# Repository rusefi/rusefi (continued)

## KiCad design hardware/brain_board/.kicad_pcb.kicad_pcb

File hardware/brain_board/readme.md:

Brain board stm 100 pin

[Forum post](https://rusefi.com/forum/viewtopic.php?f=4&t=381)

[Known issues](known_issues.txt)

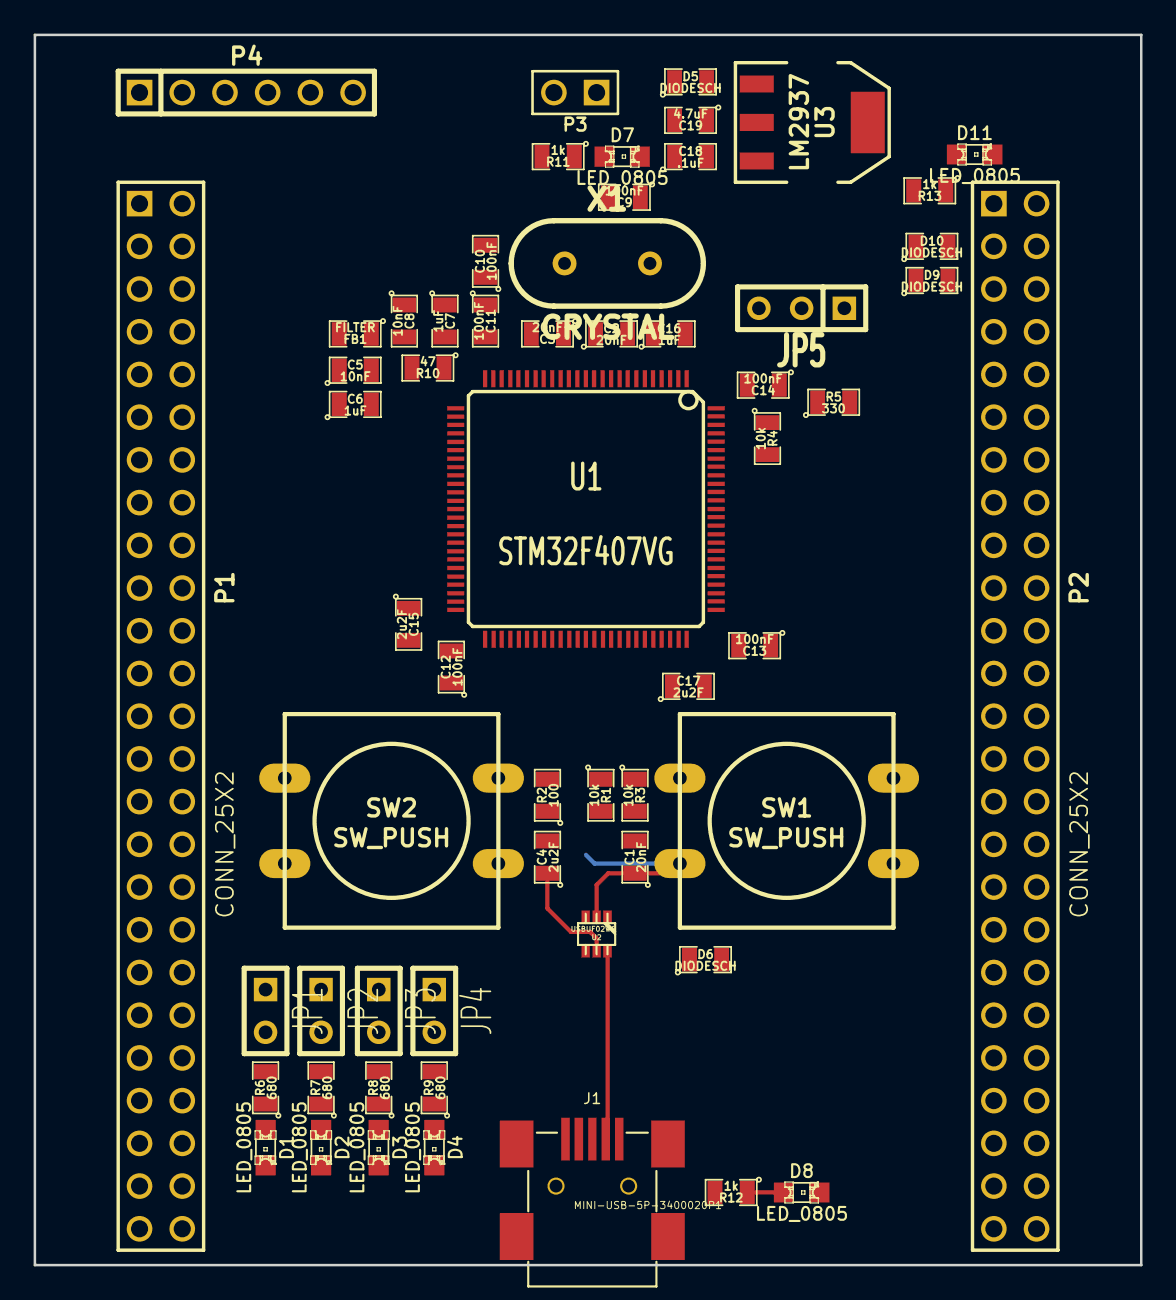
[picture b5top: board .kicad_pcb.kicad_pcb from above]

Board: 2 copper layers, 65.8 x 73.2 mm, 61 parts (1 on the bottom side), 112 nets.

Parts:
BT1: BATTERY_CR2032; BATT_CR2032_MPD
C1, C2, C3: 20nF; SM0805
C4, C15, C17: 2u2F; SM0805
C5, C8: 10nF; SM0805
C6, C7, C16: 1uF; SM0805
C9, C10, C11, C12, C13, C14: 100nF; SM0805
C18: .1uF; SM0805
C19: 4.7uF; SM0805
D1, D2, D3, D4, D7, D8, D11: LED_0805; LED-0805_A
D5, D6, D9, D10: DIODESCH; SM0805
FB1: FILTER; SM0805
J1: MINI-USB-5P-3400020P1
JP1, JP2, JP3, JP4: JUMPER; JUMPER-2
JP5: JUMPER3; SIL-3
P1, P2: CONN_25X2; PIN_ARRAY_25x2_A
P3: CONN_2; PIN_ARRAY_2_A
P4: CONN_6; PIN_ARRAY-6X1
R1, R3, R4: 10k; SM0805
R2: 100; SM0805
R5: 330; SM0805
R6, R7, R8, R9: 680; SM0805
R10: 47; SM0805
R11, R12, R13: 1k; SM0805
SW1, SW2: SW_PUSH; SW_PUSH-12mm
U1: STM32F407VG; TQFP_100
U2: USBUF02W6; sot323-6
U3: LM2937; SOT223
X1: CRYSTAL; HC-49V

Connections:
/3V: D9.2, P2.5, P2.6
/5V: D10.2, P2.3, P2.4
/5Vi: C18.2, C19.1, D5.2, D6.2, D10.1, U3.1
/BOOT0: P2.21, R4.2, U1.94
/NRST: C1.2, P1.6, P4.5, R3.2, SW1.1, U1.14
/PA0: P1.12, R5.1, U1.23
/PA1: P1.11, U1.24
/PA2: P1.14, U1.25
/PA3: P1.13, U1.26
/PA4: P1.16, U1.29
/PA5: P1.15, U1.30
/PA6: P1.18, U1.31
/PA7: P1.17, U1.32
/PA8: P2.43, U1.67
/PA9: P2.44, U1.68
/PA10: P2.41, U1.69
/PA11: U1.70, U2.3
/PA12: U1.71, U2.1
/PA13: P2.42, P4.4, U1.72
/PA14: P2.39, P4.2, U1.76
/PA15: P2.40, U1.77
/PB0: P1.22, U1.35
/PB1: P1.21, U1.36
/PB2: P1.24, U1.37
/PB3: P2.28, P4.6, U1.89
/PB4: P2.25, U1.90
/PB5: P2.26, U1.91
/PB6: P2.23, U1.92
/PB7: P2.24, U1.93
/PB8: P2.19, U1.95
/PB9: P2.20, U1.96
/PB10: P1.34, U1.47
/PB11: P1.35, U1.48
/PB12: P1.36, U1.51
/PB13: P1.37, U1.52
/PB14: P1.38, U1.53
/PB15: P1.39, U1.54
/PC0: P1.8, U1.15
/PC1: P1.7, U1.16
/PC2: P1.10, U1.17
/PC3: P1.9, U1.18
/PC4: P1.20, U1.33
/PC5: P1.19, U1.34
/PC6: P2.47, U1.63
/PC7: P2.48, U1.64
/PC8: P2.45, U1.65
/PC9: P2.46, U1.66
/PC10: P2.37, U1.78
/PC11: P2.38, U1.79
/PC12: P2.35, U1.80
/PC13: P2.12, U1.7
/PC14: P2.9, U1.8
/PC15: P2.10, U1.9
/PD0: P2.36, U1.81
/PD1: P2.33, U1.82
/PD2: P2.34, U1.83
/PD3: P2.31, U1.84
/PD4: P2.32, U1.85
/PD5: P2.29, U1.86
/PD6: P2.30, U1.87
/PD7: P2.27, U1.88
/PD8: P1.40, U1.55
/PD9: P1.41, U1.56
/PD10: P1.42, U1.57
/PD11: P1.43, U1.58
/PD12: JP1.1, P1.44, U1.59
/PD13: JP2.1, P1.45, U1.60
/PD14: JP3.1, P1.46, U1.61
/PD15: JP4.1, P1.47, U1.62
/PE0: P2.17, U1.97
/PE1: P2.18, U1.98
/PE2: P2.15, U1.1
/PE3: P2.16, U1.2
/PE4: P2.13, U1.3
/PE5: P2.14, U1.4
/PE6: P2.11, U1.5
/PE7: P1.25, U1.38
/PE8: P1.26, U1.39
/PE9: P1.27, U1.40
/PE10: P1.28, U1.41
/PE11: P1.29, U1.42
/PE12: P1.30, U1.43
/PE13: P1.31, U1.44
/PE14: P1.32, U1.45
/PE15: P1.33, U1.46
/VDD: C4.1, C9.2, C10.2, C11.2, C12.2, C13.2, C14.2, C16.2, D9.1, FB1.2, JP5.1, P1.3, P1.4, P2.22, P4.1, R3.1, R13.2, SW2.2, U1.11, U1.19, U1.28, U1.50, U1.75, U1.100, U2.5, U3.3
GND: BT1.2, C1.1, C2.2, C3.2, C5.1, C6.1, C7.1, C8.1, C9.1, C10.1, C11.1, C12.1, C13.1, C14.1, C15.2, C16.1, C17.2, C18.1, C19.2, D1.2, D2.2, D3.2, D4.2, D7.2, D8.2, D11.2, J1.5, P1.1, P1.2, P1.5, P1.23, P1.49, P1.50, P2.1, P2.2, P2.49, P2.50, P3.2, P4.3, R1.2, R4.1, SW1.2, U1.10, U1.20, U1.27, U1.74, U1.99, U2.2, U3.2, U3.4
unnamed: D7.1, R11.1
unnamed: D8.1, R12.1
unnamed: D6.1, J1.1, R12.2
unnamed: D5.1, P3.1, R11.2
unnamed: C4.2, R2.1
unnamed: R1.1, R2.2, R5.2, SW2.1
unnamed: D1.1, R6.1
unnamed: D2.1, R7.1
unnamed: D3.1, R8.1
unnamed: D4.1, R9.1
unnamed: JP1.2, R6.2
unnamed: C3.1, U1.13, X1.1
unnamed: C2.1, U1.12, X1.2
unnamed: C7.2, FB1.1, R10.1, U1.22
unnamed: C5.2, C6.2, R10.2, U1.21
unnamed: J1.2, U2.6
unnamed: J1.3, U2.4
unnamed: JP2.2, R7.2
unnamed: JP4.2, R9.2
unnamed: JP3.2, R8.2
unnamed: JP5.2, U1.6
unnamed: BT1.1, JP5.3
unnamed: D11.1, R13.1
unnamed: C17.1, U1.73
unnamed: C15.1, U1.49
